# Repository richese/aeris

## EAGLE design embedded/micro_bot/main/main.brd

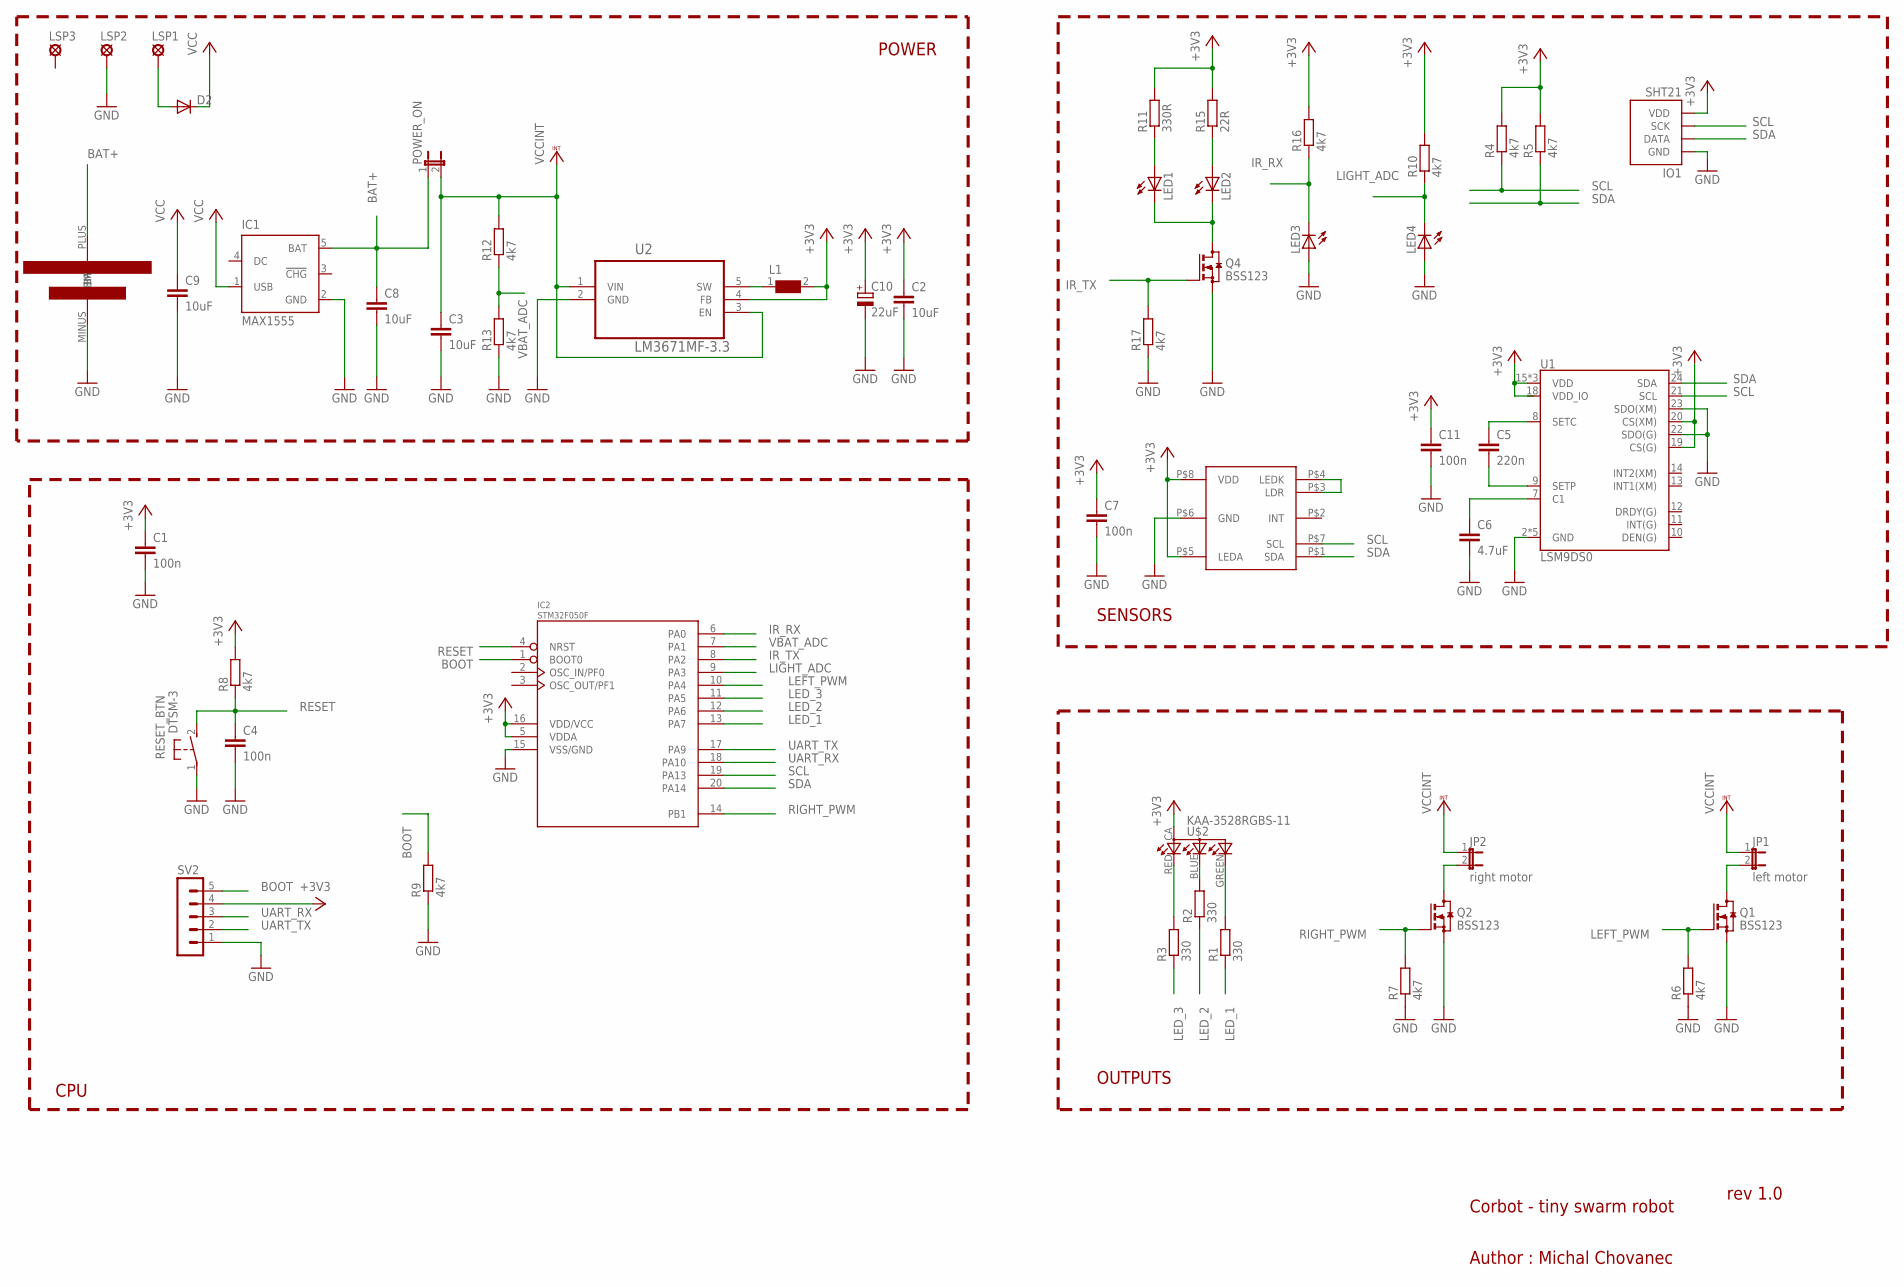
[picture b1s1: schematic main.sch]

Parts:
C1, C4, C7, C11: 100n; C0805
C2, C3, C8, C9: 10uF; C0805
C5: 220n; C0805
C6: 4.7uF; C0805
C10: 22uF; 153CLV-0505
D2: DIODE-DO-214AC; DO-214AC
IC1: MAX1555; SOT23-5L
IC2: STM32F050F; TSSOP20
IO1: SHT21; SHT2X
JP1: left motor; JP1
JP2: right motor; JP1
L1: WE-LQ-744032002_M; WE-LQ_M
LED1, LED2, LED3, LED4: LEDCHIPLED_1206; CHIPLED_1206
LSP1, LSP2, LSP3: LSP13
POWER_ON: JP1E; JP1
Q1, Q2, Q4: BSS123; SOT23
R1, R2, R3: 330; M0805
R4, R5, R6, R7, R8, R9, R10, R12, R13, R16, R17: 4k7; M0805
R11: 330R; M0805
R15: 22R; M0805
RESET_BTN: DTSM-3
SV2: MA05-1
U1: LSM9DS0; LGA-24
U2: LM3671MF-3.3; SOT95P284X122-5N
U$1: SMTU_2450N
U$2: KAA-3528RGBS-11; LED-RGB
U$3: APDS9950

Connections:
+3V3: C1.1, C2.1, C7.1, C10.+, C11.1, IC2.5 (VDDA), IC2.16 (VDD/VCC), IO1.5 (VDD), L1.2, R4.2, R5.2, R8.2, R10.2, R11.2, R15.2, R16.2, SV2.4, U1.15 (VDD), U1.16 (VDD), U1.17 (VDD), U1.19 (CS(G)), U1.20 (CS(XM)), U2.4 (FB), U$2.CA (A), U$3.P$5 (LEDA), U$3.P$8 (VDD)
BAT+: C8.1, IC1.5 (BAT), POWER_ON.1, U$1.PLUS (BP)
BOOT: IC2.1 (BOOT0), R9.2, SV2.5
GND: C1.2, C2.2, C3.2, C4.2, C6.2, C7.2, C8.2, C9.2, C10.-, C11.2, IC1.2 (GND), IC2.15 (VSS/GND), IO1.2 (GND), LED3.A, LED4.A, LSP2.MP, Q1.2 (S), Q2.2 (S), Q4.2 (S), R6.1, R7.1, R9.1, R13.1, R17.1, RESET_BTN.1, SV2.1, U1.2 (GND), U1.3 (GND), U1.4 (GND), U1.5 (GND), U1.6 (GND), U1.22 (SDO(G)), U1.23 (SDO(XM)), U2.2 (GND), U$1.MINUS (BM), U$3.P$6 (GND)
IR_RX: IC2.6 (PA0), LED3.C, R16.1
IR_TX: IC2.8 (PA2), Q4.1 (G), R17.2
LED_1: IC2.13 (PA7), R1.1
LED_2: IC2.12 (PA6), R2.1
LED_3: IC2.11 (PA5), R3.1
LEFT_PWM: IC2.10 (PA4), Q1.1 (G), R6.2
LIGHT_ADC: IC2.9 (PA3), LED4.C, R10.1
unnamed: R3.2, U$2.RED (CRED)
unnamed: R2.2, U$2.BLUE (CBLUE)
unnamed: R1.2, U$2.GREEN (CGREEN)
unnamed: U$3.P$3 (LDR), U$3.P$4 (LEDK)
unnamed: C6.1, U1.7 (C1)
unnamed: LED1.C, LED2.C, Q4.3 (D)
unnamed: L1.1, U2.5 (SW)
unnamed: C5.1, U1.8 (SETC)
unnamed: D2.A, LSP1.MP
unnamed: LED2.A, R15.1
unnamed: C5.2, U1.9 (SETP)
unnamed: JP1.2, Q1.3 (D)
unnamed: JP2.2, Q2.3 (D)
unnamed: LED1.A, R11.1
RESET: C4.1, IC2.4 (NRST), R8.1, RESET_BTN.2
RIGHT_PWM: IC2.14 (PB1), Q2.1 (G), R7.2
SCL: IC2.19 (PA13), IO1.4 (SCK), R4.1, U1.21 (SCL), U$3.P$7 (SCL)
SDA: IC2.20 (PA14), IO1.1 (DATA), R5.1, U1.24 (SDA), U$3.P$1 (SDA)
UART_RX: IC2.18 (PA10), SV2.3
UART_TX: IC2.17 (PA9), SV2.2
VBAT_ADC: IC2.7 (PA1), R12.1, R13.2
VCC: C9.1, D2.C, IC1.1 (USB)
VCCINT: C3.1, JP1.1, JP2.1, POWER_ON.2, R12.2, U2.1 (VIN), U2.3 (EN)

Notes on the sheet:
CPU
POWER
SENSORS
OUTPUTS
Corbot - tiny swarm robot
rev 1.0
Author : Michal Chovanec

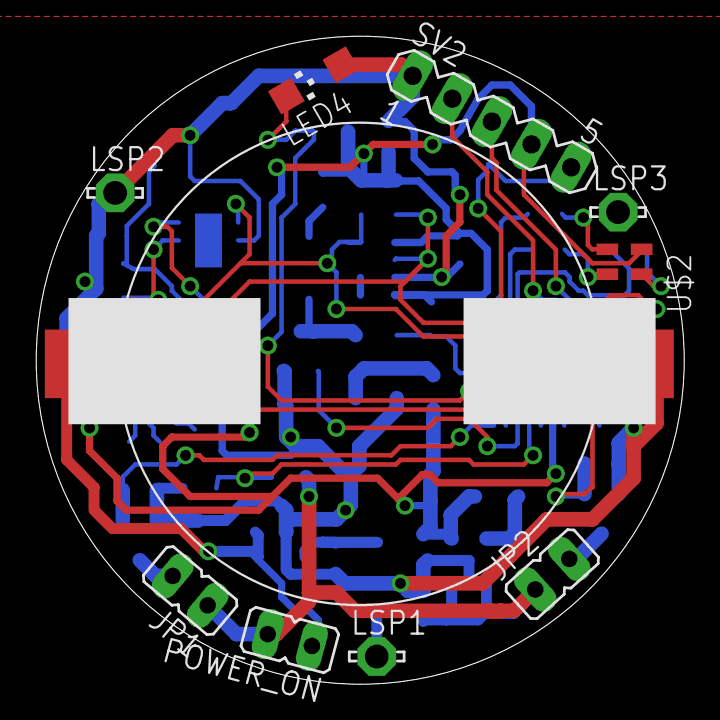
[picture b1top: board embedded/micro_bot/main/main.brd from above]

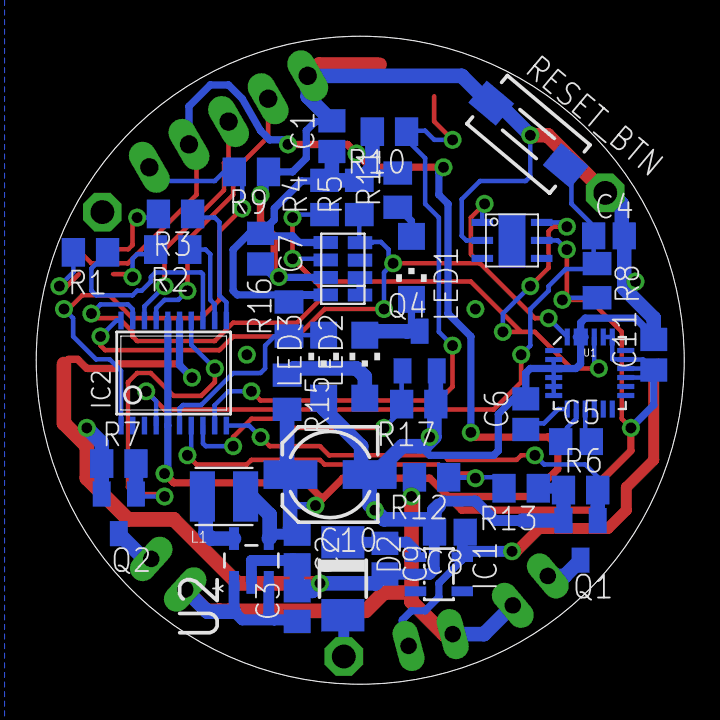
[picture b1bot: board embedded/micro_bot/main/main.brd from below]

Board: 2 copper layers, 36.0 x 36.0 mm, 52 parts (42 on the bottom side), 34 nets.

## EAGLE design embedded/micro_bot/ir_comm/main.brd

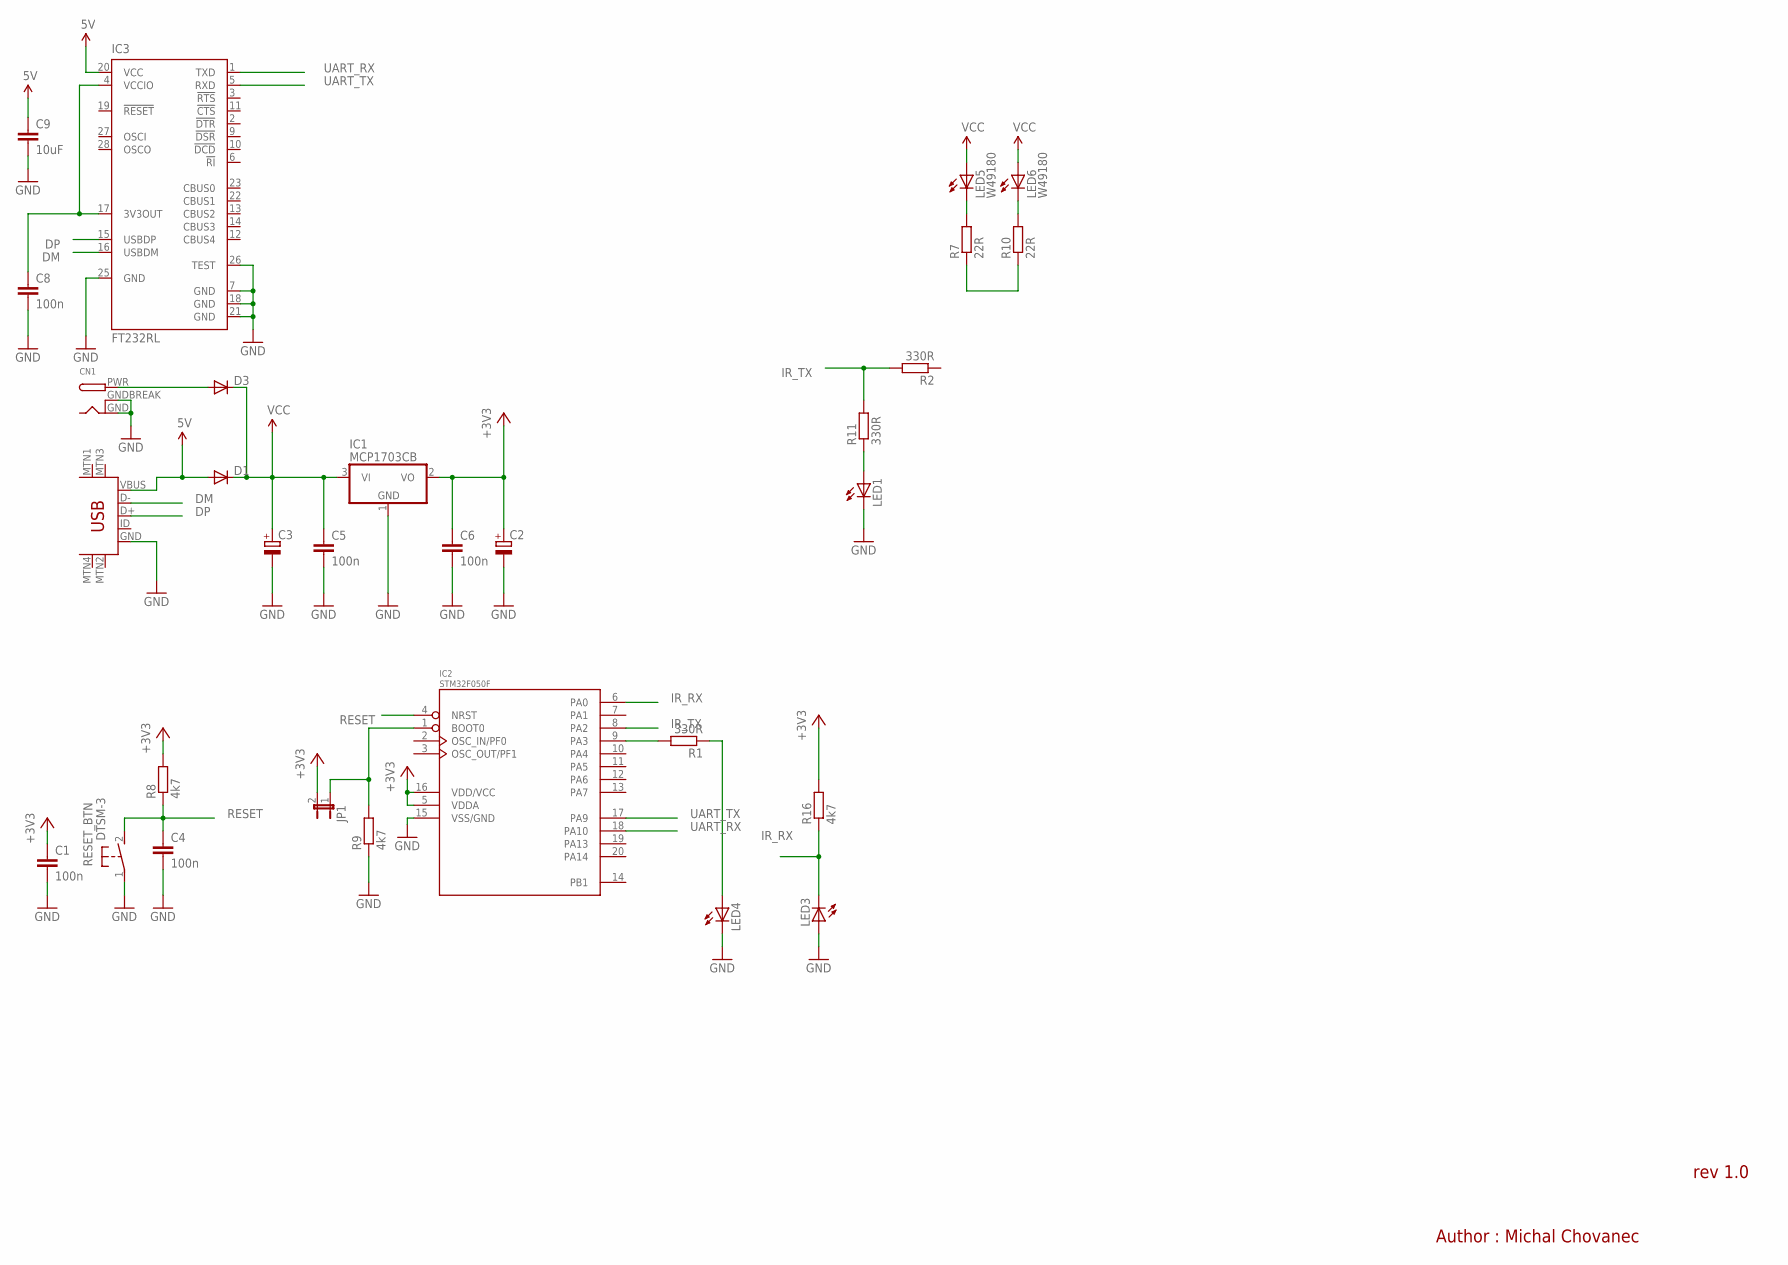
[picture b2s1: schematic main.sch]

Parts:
C1, C4, C5, C6, C8: 100n; C0805
C2: CPOL-EU153CLV-0405; 153CLV-0405
C3: CPOL-EU150CLZ-1010; 150CLZ-1010
C9: 10uF; C0805
CN1: DCBARRELPTH; DCJACK_2MM_PTH
D1, D3: DIODE-DO-214AC; DO-214AC
IC1: MCP1703CB; SOT23
IC2: STM32F050F; TSSOP20
IC3: FT232RL; SSOP28
JP1: JP1E; JP1
LED1, LED3, LED4: LEDCHIPLED_1206; CHIPLED_1206
LED5, LED6: W49180; Z-POWER-LED-DOME-TYPE
R1, R2, R11: 330R; M0805
R7, R10: 22R; M0805
R8, R9, R16: 4k7; M0805
RESET_BTN: DTSM-3
U$1: USB-MINIB-5PIN; USB-MINIB

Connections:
5V: C9.1, D1.A, IC3.20 (VCC), U$1.VBUS
+3V3: C1.1, C2.+, C6.1, IC1.2 (VO), IC2.5 (VDDA), IC2.16 (VDD/VCC), JP1.2, R8.2, R16.2
BOOT: IC2.1 (BOOT0), JP1.1, R9.2
DM: IC3.16 (USBDM), U$1.D-
DP: IC3.15 (USBDP), U$1.D+
GND: C1.2, C2.-, C3.-, C4.2, C5.2, C6.2, C8.2, C9.2, CN1.GND, CN1.GNDBREAK, IC1.1 (GND), IC2.15 (VSS/GND), IC3.7 (GND), IC3.18 (GND), IC3.21 (GND), IC3.25 (GND), IC3.26 (TEST), LED1.C, LED3.A, LED4.C, R9.1, RESET_BTN.1, U$1.GND
IR_RX: IC2.6 (PA0), LED3.C, R16.1
IR_TX: IC2.8 (PA2), R2.2, R11.2
unnamed: IC2.9 (PA3), R1.2
unnamed: C8.1, IC3.4 (VCCIO), IC3.17 (3V3OUT)
unnamed: LED1.A, R11.1
unnamed: CN1.PWR, D3.A
unnamed: LED4.A, R1.1
unnamed: LED5.C, R7.2
unnamed: LED6.C, R10.2
unnamed: R7.1, R10.1
RESET: C4.1, IC2.4 (NRST), R8.1, RESET_BTN.2
UART_RX: IC2.18 (PA10), IC3.1 (TXD)
UART_TX: IC2.17 (PA9), IC3.5 (RXD)
VCC: C3.+, C5.1, D1.C, D3.C, IC1.3 (VI), LED5.A, LED6.A

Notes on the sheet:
rev 1.0
Author : Michal Chovanec

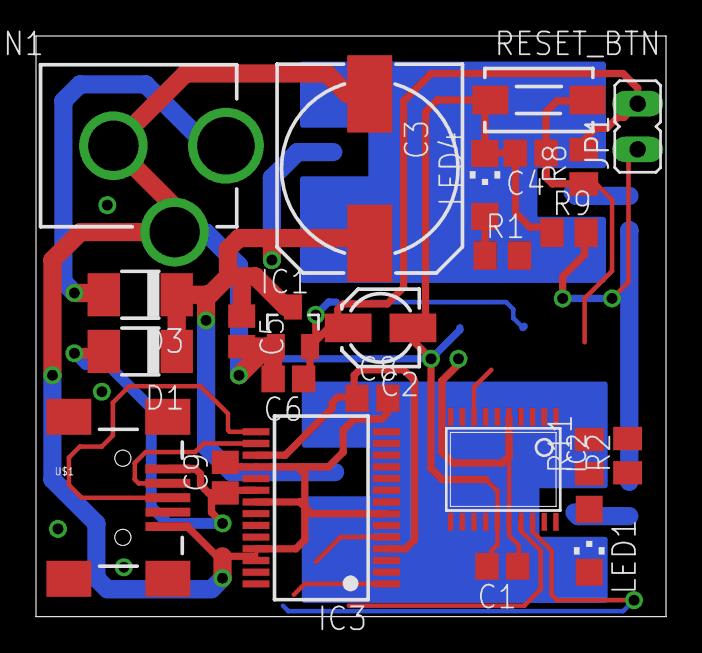
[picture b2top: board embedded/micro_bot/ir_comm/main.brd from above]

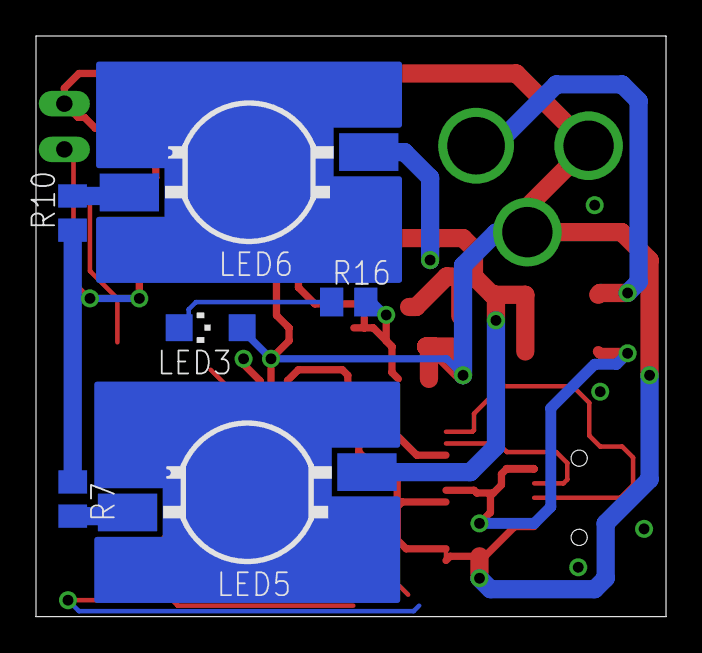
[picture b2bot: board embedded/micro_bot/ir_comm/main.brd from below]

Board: 2 copper layers, 35.0 x 32.3 mm, 30 parts (6 on the bottom side), 20 nets.

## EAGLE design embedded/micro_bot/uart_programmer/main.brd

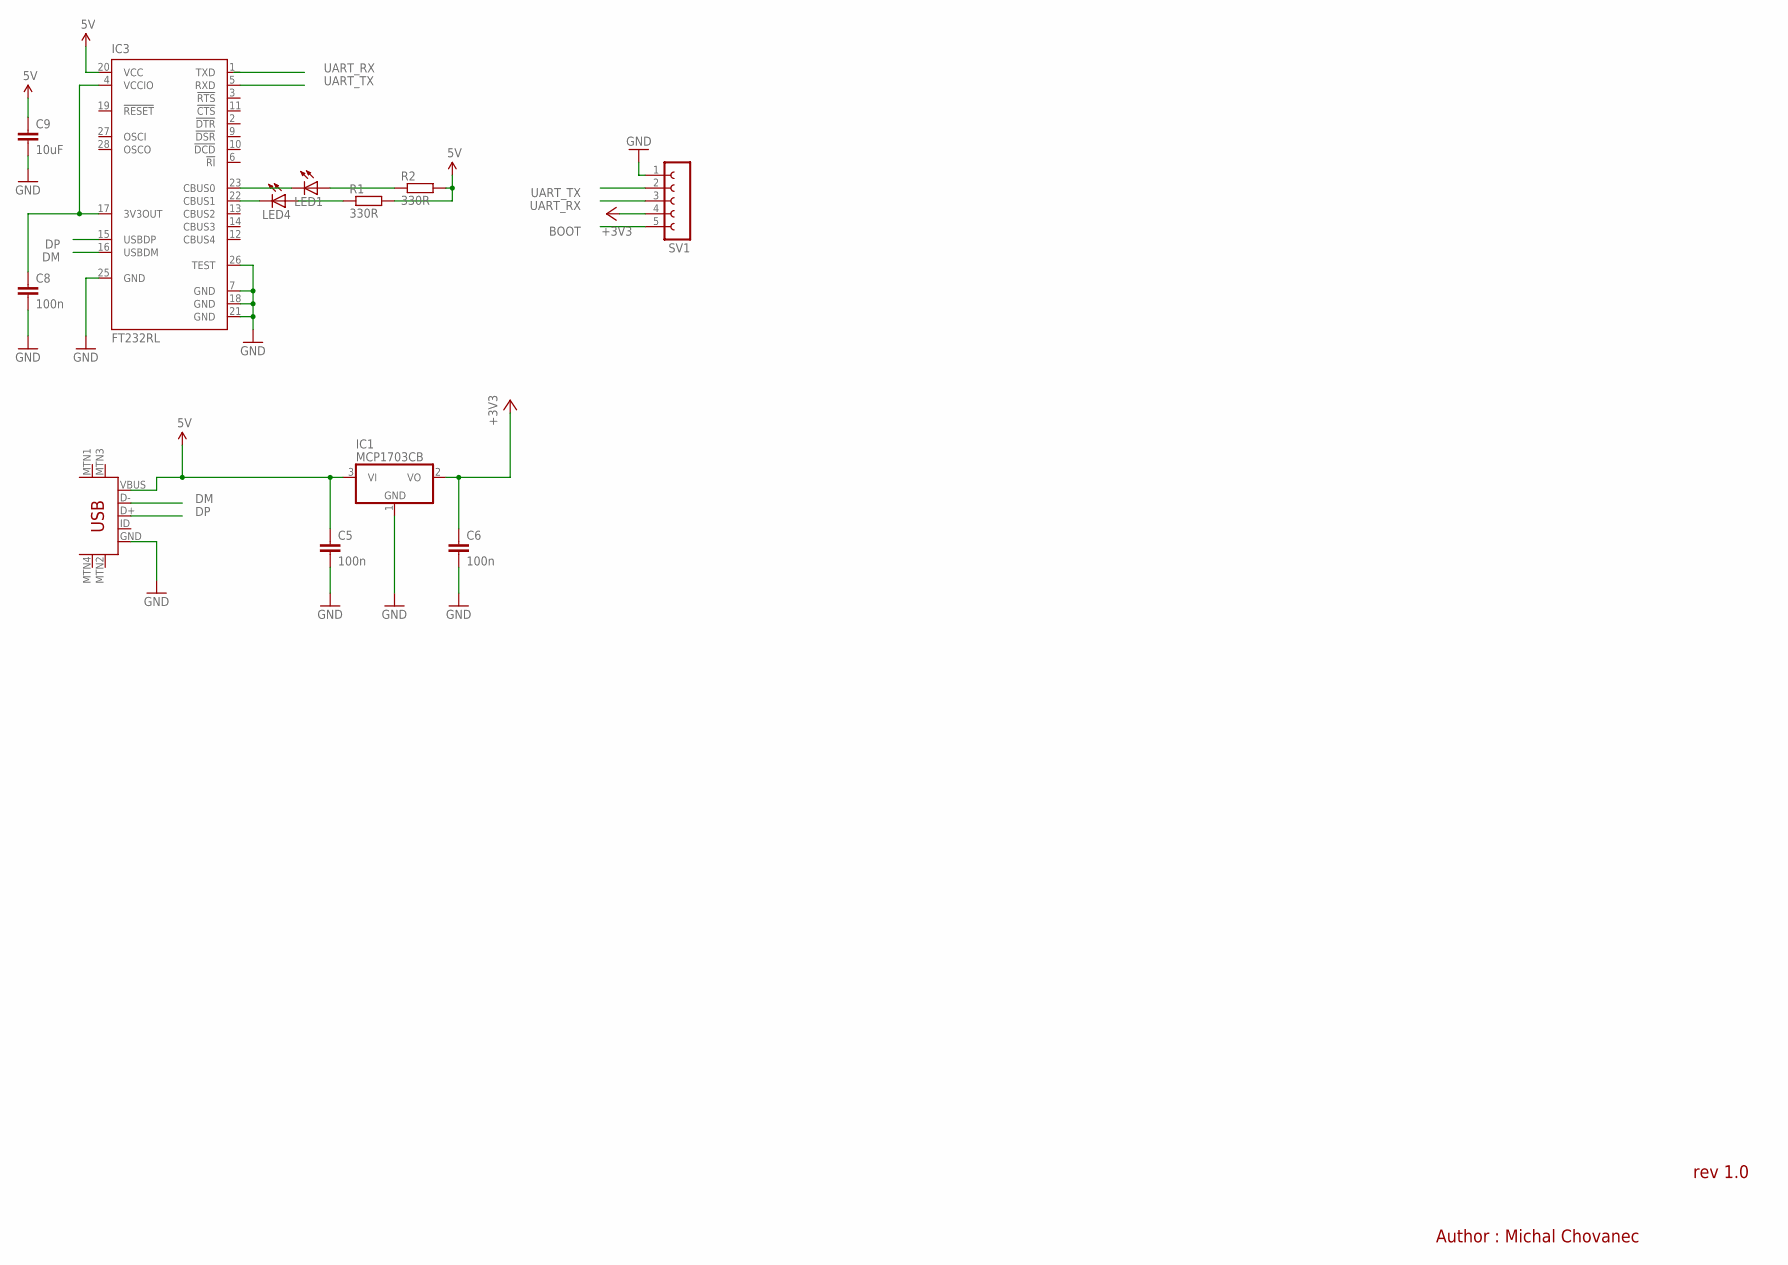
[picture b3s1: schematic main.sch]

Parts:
C5, C6, C8: 100n; C0805
C9: 10uF; C0805
IC1: MCP1703CB; SOT23
IC3: FT232RL; SSOP28
LED1, LED4: LEDCHIPLED_1206; CHIPLED_1206
R1, R2: 330R; M0805
SV1: FE05-1
U$1: USB-MINIB-5PIN; USB-MINIB

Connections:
5V: C5.1, C9.1, IC1.3 (VI), IC3.20 (VCC), R1.2, R2.2, U$1.VBUS
+3V3: C6.1, IC1.2 (VO), SV1.4
BOOT: SV1.5
DM: IC3.16 (USBDM), U$1.D-
DP: IC3.15 (USBDP), U$1.D+
GND: C5.2, C6.2, C8.2, C9.2, IC1.1 (GND), IC3.7 (GND), IC3.18 (GND), IC3.21 (GND), IC3.25 (GND), IC3.26 (TEST), SV1.1, U$1.GND
unnamed: IC3.23 (CBUS0), LED1.C
unnamed: C8.1, IC3.4 (VCCIO), IC3.17 (3V3OUT)
unnamed: IC3.22 (CBUS1), LED4.C
unnamed: LED4.A, R1.1
unnamed: LED1.A, R2.1
UART_RX: SV1.3
UART_TX: IC3.5 (RXD), SV1.2

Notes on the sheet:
rev 1.0
Author : Michal Chovanec

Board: 2 copper layers, 12 parts (0 on the bottom side), 11 nets, no tracks yet.

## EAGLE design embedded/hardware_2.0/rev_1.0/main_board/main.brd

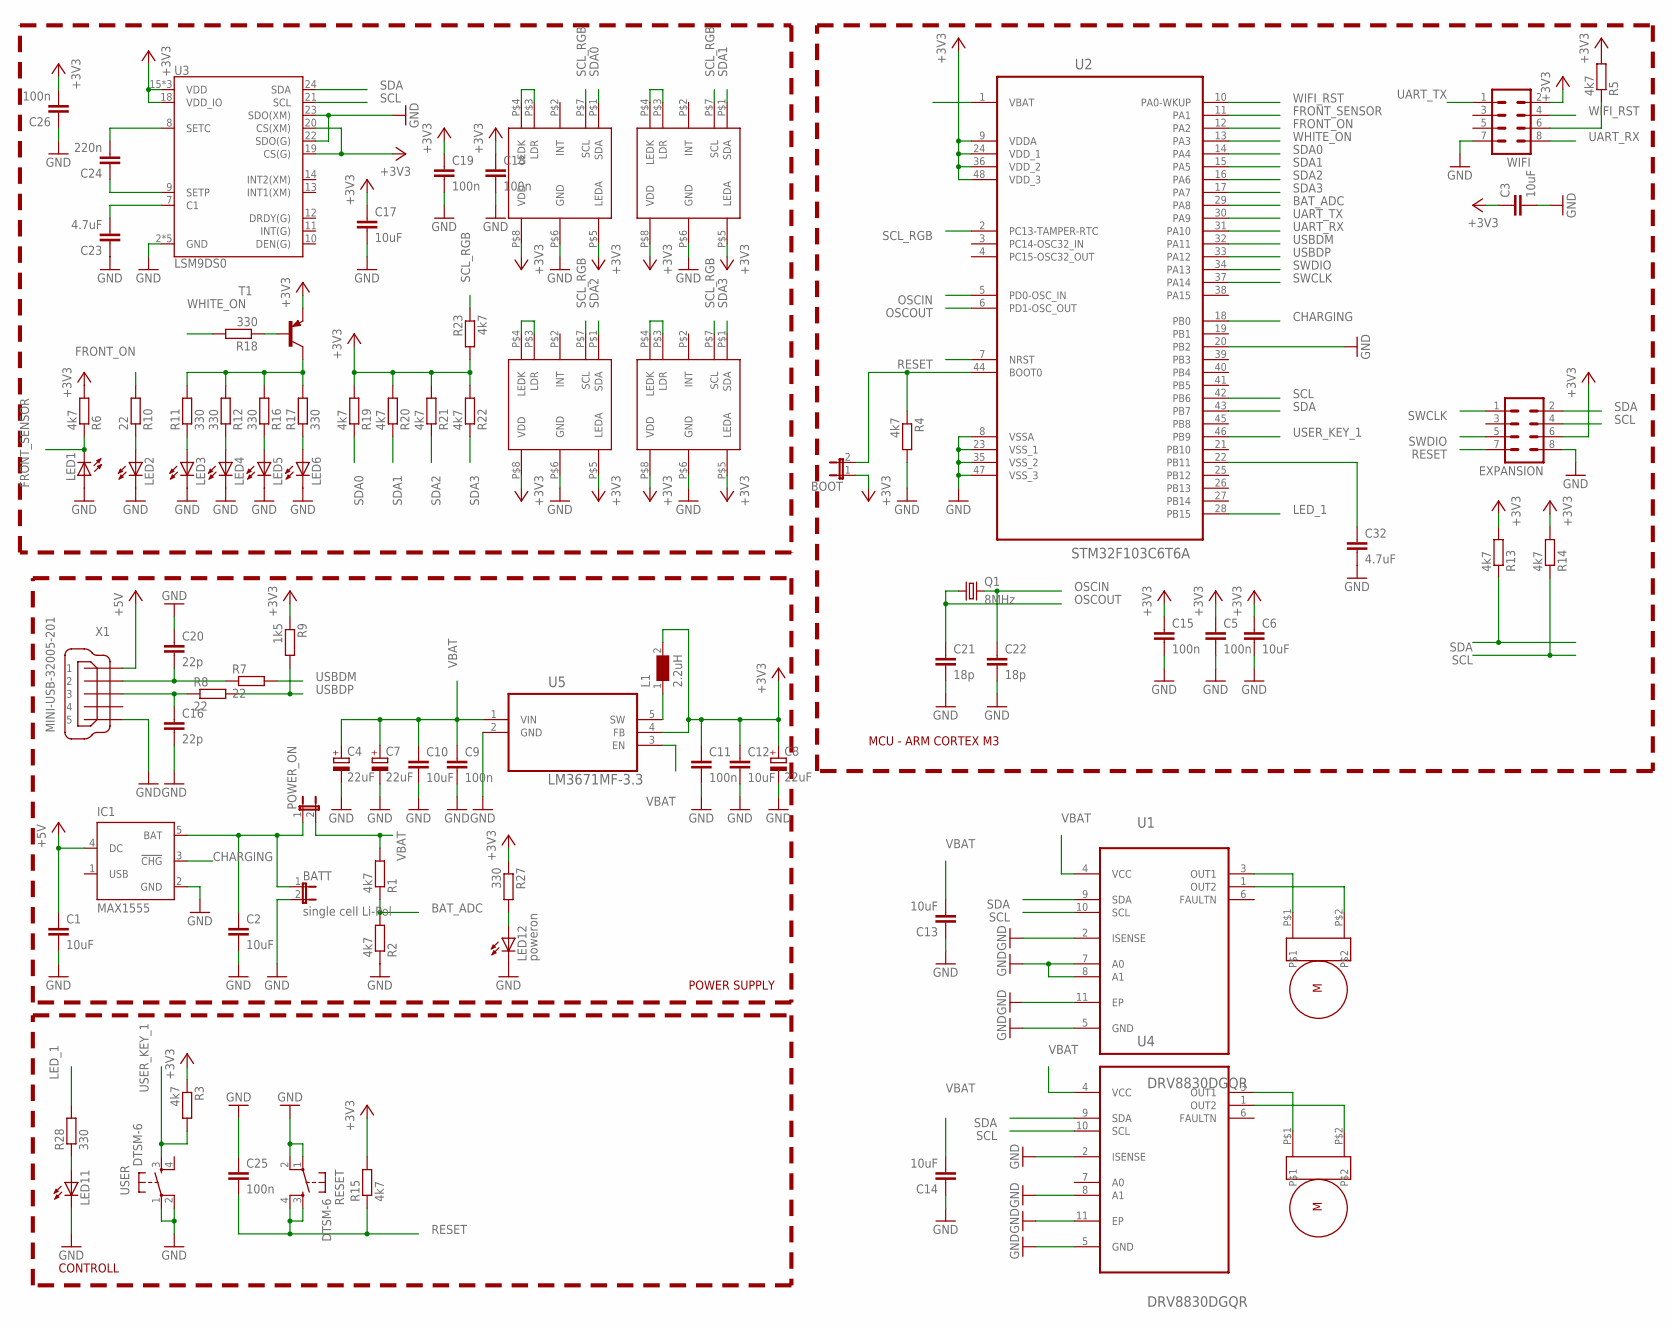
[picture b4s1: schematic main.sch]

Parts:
BATT: single cell Li-Pol; JP1
BOOT: JP1E; JP1
C1, C2, C3, C6, C10, C12, C13, C14, C17: 10uF; C0805
C4, C7, C8: 22uF; 153CLV-0505
C5, C9, C11, C15, C18, C19, C25, C26: 100n; C0805
C16, C20: 22p; C0805
C21, C22: 18p; C0805
C23, C32: 4.7uF; C0805
C24: 220n; C0805
EXPANSION: MA04-2
IC1: MAX1555; SOT23-5L
L1: 2.2uH; WE-LQ_M
LED1, LED2: LED5MM
LED3, LED4, LED5, LED6, LED11: LEDCHIPLED_1206; CHIPLED_1206
LED12: poweron; CHIPLED_1206
POWER_ON: JP1E; JP1
Q1: 8MHz; CTS406
R1, R2, R3, R4, R5, R6, R13, R14, R15, R19, R20, R21, R22, R23: 4k7; M0805
R7, R8, R10: 22; M0805
R9: 1k5; M0805
R11, R12, R16, R17, R18, R27, R28: 330; M0805
RESET: DTSM-6
T1: BC857A-PNP-SOT23-BEC; SOT23-BEC
U1, U4: DRV8830DGQR; SOP65P640X110-15N
U2: STM32F103C6T6A; QFP50P900X900X160-48N
U3: LSM9DS0; LGA-24
U5: LM3671MF-3.3; SOT95P284X122-5N
U$1, U$2, U$3, U$4: APDS9950
U$5, U$6: MICRO_METAL_GEAR_MOTOR
USER: DTSM-6
WIFI: MA04-2
X1: MINI-USB-32005-201; 32005-201

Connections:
+3V3: BOOT.1, C3.1, C5.1, C6.1, C8.+, C11.1, C12.1, C15.1, C17.1, C18.1, C19.1, C26.2, EXPANSION.6, L1.2, R3.1, R5.2, R6.2, R9.1, R13.2, R14.2, R15.2, R19.2, R20.2, R21.2, R22.2, R23.2, R27.1, T1.E, U2.9 (VDDA), U2.24 (VDD_1), U2.36 (VDD_2), U2.48 (VDD_3), U3.15 (VDD), U3.16 (VDD), U3.17 (VDD), U3.18 (VDD_IO), U3.19 (CS(G)), U3.20 (CS(XM)), U5.4 (FB), U$1.P$5 (LEDA), U$1.P$8 (VDD), U$2.P$5 (LEDA), U$2.P$8 (VDD), U$3.P$5 (LEDA), U$3.P$8 (VDD), U$4.P$5 (LEDA), U$4.P$8 (VDD), WIFI.2
+5V: C1.1, IC1.4 (DC), X1.1
BAT_ADC: R1.1, R2.2, U2.29 (PA8)
CHARGING: IC1.3 (!CHG), U2.18 (PB0)
FRONT_ON: R10.2, U2.12 (PA2)
FRONT_SENSOR: LED1.K (C), R6.1, U2.11 (PA1)
GND: BATT.2, C1.2, C2.2, C3.2, C4.-, C5.2, C6.2, C7.-, C8.-, C9.2, C10.2, C11.2, C12.2, C13.1, C14.1, C15.2, C16.2, C17.2, C18.2, C19.2, C20.1, C21.2, C22.2, C23.1, C25.1, C26.1, C32.2, EXPANSION.8, IC1.2 (GND), LED1.A, LED2.K (C), LED3.C, LED4.C, LED5.C, LED6.C, LED11.C, LED12.C, R2.1, R4.2, RESET.1, RESET.2, U1.2 (ISENSE), U1.5 (GND), U1.7 (A0), U1.8 (A1), U1.11 (EP), U2.8 (VSSA), U2.20 (PB2), U2.23 (VSS_1), U2.35 (VSS_2), U2.47 (VSS_3), U3.2 (GND), U3.3 (GND), U3.4 (GND), U3.5 (GND), U3.6 (GND), U3.22 (SDO(G)), U3.23 (SDO(XM)), U4.2 (ISENSE), U4.5 (GND), U4.8 (A1), U4.11 (EP), U5.2 (GND), U$1.P$6 (GND), U$2.P$6 (GND), U$3.P$6 (GND), U$4.P$6 (GND), USER.1, USER.2, WIFI.7, X1.5
LED_1: R28.2, U2.28 (PB15)
unnamed: R5.1, WIFI.6
unnamed: BATT.1, C2.1, IC1.5 (BAT), POWER_ON.1
unnamed: U1.1 (OUT2), U$5.P$2
unnamed: U1.3 (OUT1), U$5.P$1
unnamed: U4.1 (OUT2), U$6.P$2
unnamed: C23.2, U3.7 (C1)
unnamed: C24.2, U3.8 (SETC)
unnamed: U4.3 (OUT1), U$6.P$1
unnamed: L1.1, U5.5 (SW)
unnamed: C24.1, U3.9 (SETP)
unnamed: C32.1, U2.22 (PB11)
unnamed: LED3.A, R11.1
unnamed: BOOT.2, R4.1, U2.44 (BOOT0)
unnamed: U$1.P$3 (LDR), U$1.P$4 (LEDK)
unnamed: U$2.P$3 (LDR), U$2.P$4 (LEDK)
unnamed: U$3.P$3 (LDR), U$3.P$4 (LEDK)
unnamed: U$4.P$3 (LDR), U$4.P$4 (LEDK)
unnamed: LED2.A, R10.1
unnamed: LED4.A, R12.1
unnamed: LED12.A, R27.2
unnamed: LED5.A, R16.1
unnamed: LED6.A, R17.1
unnamed: R11.2, R12.2, R16.2, R17.2, T1.C
unnamed: R18.1, T1.B
unnamed: LED11.A, R28.1
unnamed: C20.2, R7.1, X1.2
unnamed: C16.1, R8.1, X1.3
NC: U2.1 (VBAT)
OSCIN: C22.1, Q1.3 (2), U2.5 (PD0-OSC_IN)
OSCOUT: C21.1, Q1.1, U2.6 (PD1-OSC_OUT)
RESET: C25.2, EXPANSION.7, R15.1, RESET.3, RESET.4, U2.7 (NRST)
SCL: EXPANSION.4, R14.1, U1.10 (SCL), U2.42 (PB6), U3.21 (SCL), U4.10 (SCL)
SCL_RGB: R23.1, U2.2 (PC13-TAMPER-RTC), U$1.P$7 (SCL), U$2.P$7 (SCL), U$3.P$7 (SCL), U$4.P$7 (SCL)
SDA: EXPANSION.2, R13.1, U1.9 (SDA), U2.43 (PB7), U3.24 (SDA), U4.9 (SDA)
SDA0: R19.1, U2.14 (PA4), U$1.P$1 (SDA)
SDA1: R20.1, U2.15 (PA5), U$2.P$1 (SDA)
SDA2: R21.1, U2.16 (PA6), U$3.P$1 (SDA)
SDA3: R22.1, U2.17 (PA7), U$4.P$1 (SDA)
SWCLK: EXPANSION.1, U2.37 (PA14)
SWDIO: EXPANSION.5, U2.34 (PA13)
UART_RX: U2.31 (PA10), WIFI.8
UART_TX: U2.30 (PA9), WIFI.1
USBDM: R7.2, U2.32 (PA11)
USBDP: R8.2, R9.2, U2.33 (PA12)
USER_KEY_1: R3.2, U2.46 (PB9), USER.3
VBAT: C4.+, C7.+, C9.1, C10.1, C13.2, C14.2, POWER_ON.2, R1.2, U1.4 (VCC), U4.4 (VCC), U5.1 (VIN), U5.3 (EN)
WHITE_ON: R18.2, U2.13 (PA3)
WIFI_RST: U2.10 (PA0-WKUP), WIFI.4

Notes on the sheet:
POWER SUPPLY
CONTROLL
MCU - ARM CORTEX M3

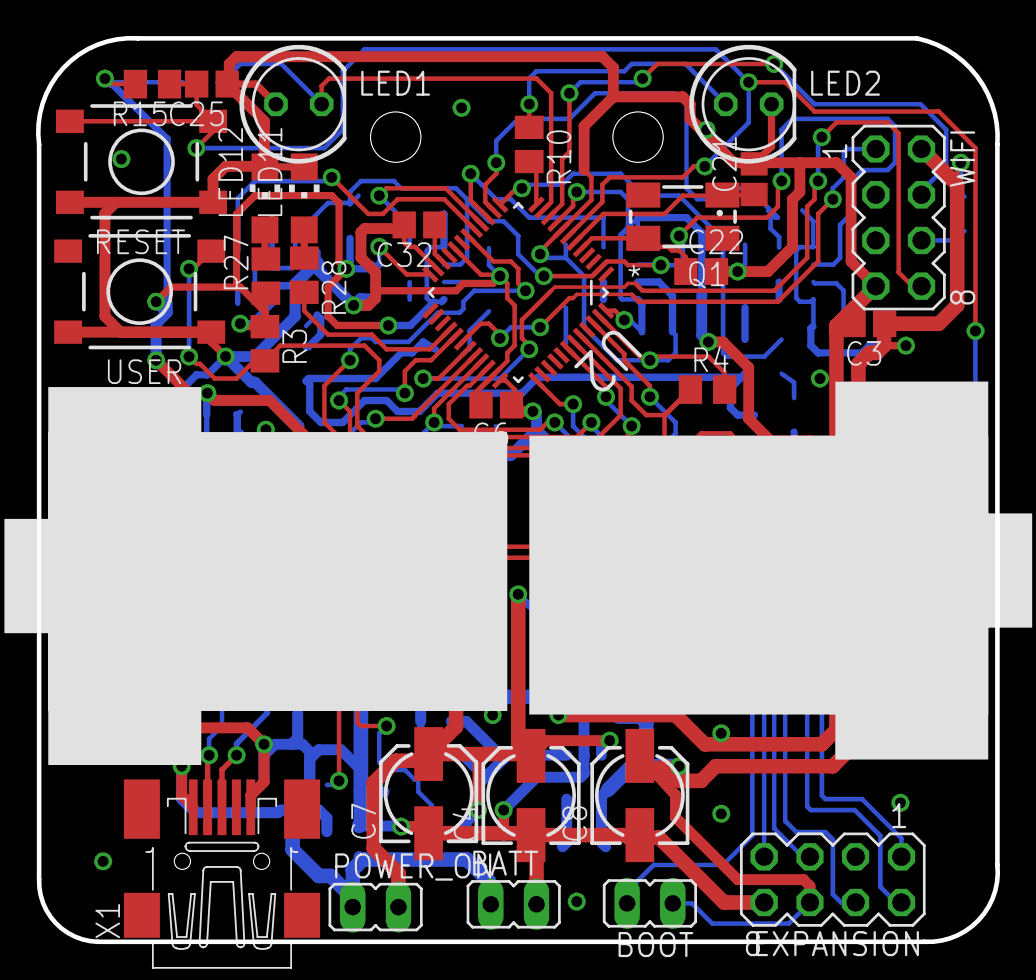
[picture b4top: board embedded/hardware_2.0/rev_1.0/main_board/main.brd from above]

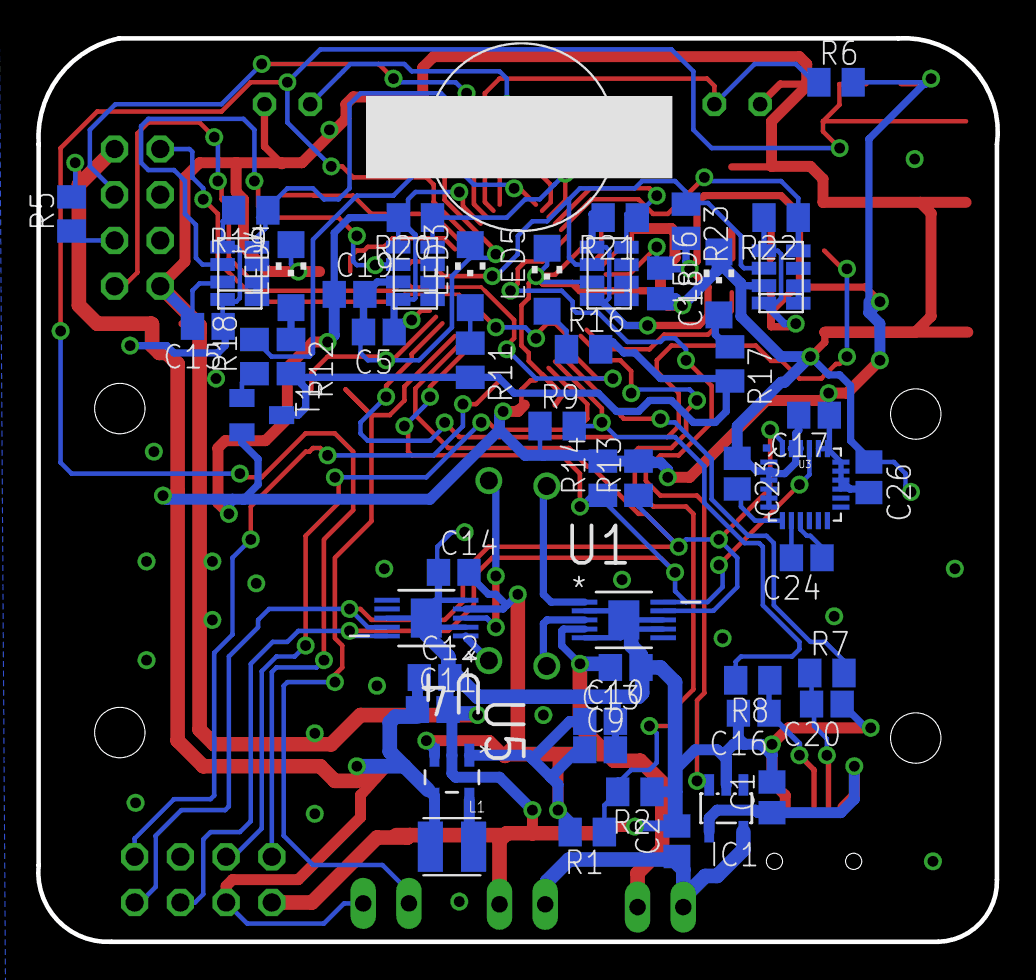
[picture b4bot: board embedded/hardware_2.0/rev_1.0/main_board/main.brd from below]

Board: 2 copper layers, 53.3 x 50.2 mm, 84 parts (53 on the bottom side), 55 nets.

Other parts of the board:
U$7: BALL_3/8

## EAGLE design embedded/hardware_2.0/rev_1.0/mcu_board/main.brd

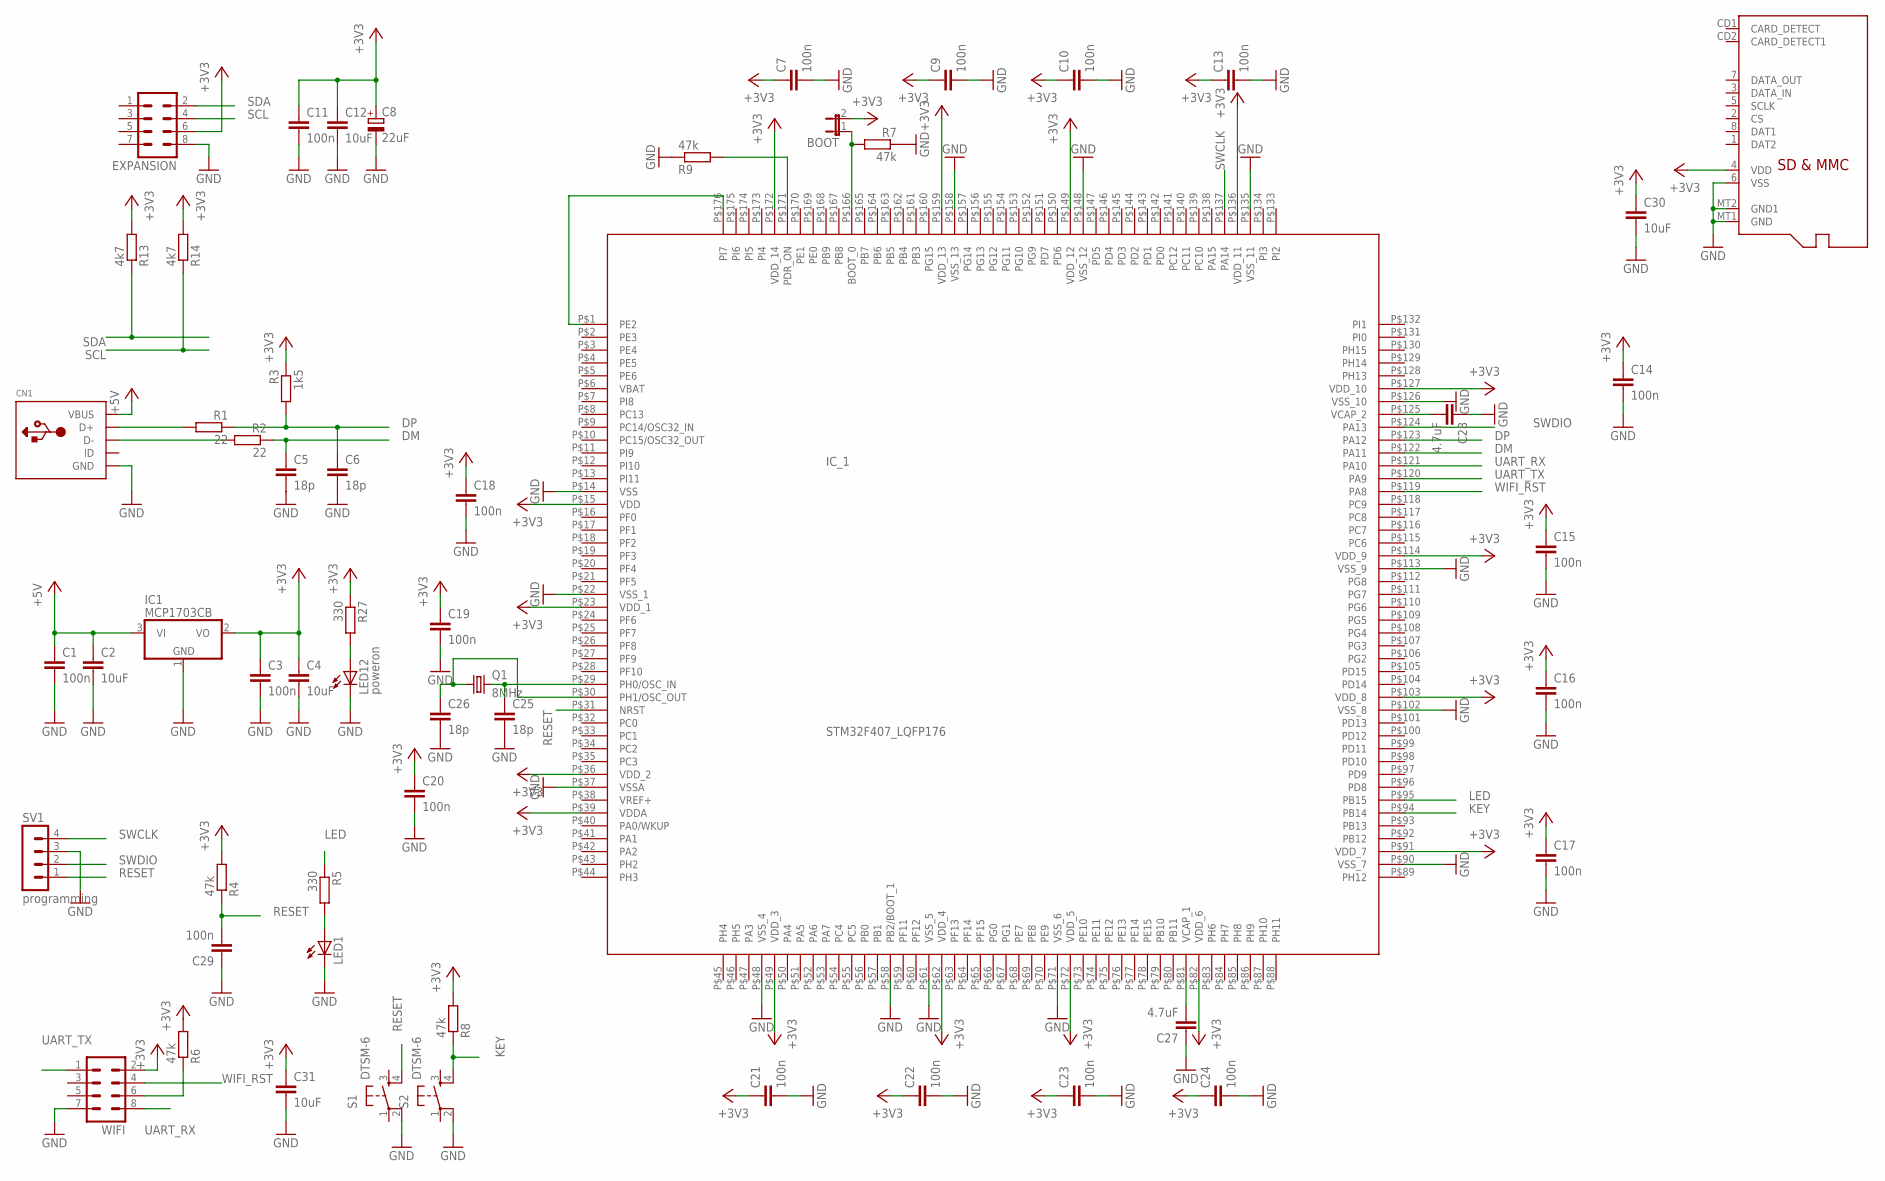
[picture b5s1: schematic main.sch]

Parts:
BOOT: JP1E; JP1
C1, C3, C7, C9, C10, C11, C13, C14, C15, C16, C17, C18, C19, C20, C21, C22, C23, C24, C29: 100n; C0805
C2, C4, C12, C30, C31: 10uF; C0805
C5, C6, C25, C26: 18p; C0805
C8: 22uF; 153CLV-0505
C27, C28: 4.7uF; C0805
CN1: USBMINIB; USB-MINIB
EXPANSION: MA04-2
IC1: MCP1703CB; SOT23
IC_1: STM32F407_LQFP176
LED1: LEDCHIPLED_1206; CHIPLED_1206
LED12: poweron; CHIPLED_1206
Q1: 8MHz; CTS406
R1, R2: 22; M0805
R3: 1k5; M0805
R4, R6, R7, R8, R9: 47k; M0805
R5, R27: 330; M0805
R13, R14: 4k7; M0805
S1, S2: DTSM-6
SV1: programming; MA04-1
U$1: MICROSD
WIFI: MA04-2

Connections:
+3V3: BOOT.2, C3.1, C4.1, C7.1, C8.+, C9.1, C10.1, C11.1, C12.1, C13.1, C14.1, C15.1, C16.1, C17.1, C18.1, C19.1, C20.1, C21.1, C22.1, C23.1, C24.1, C30.1, C31.1, EXPANSION.6, IC1.2 (VO), IC_1.P$15 (VDD), IC_1.P$23 (VDD_1), IC_1.P$36 (VDD_2), IC_1.P$39 (VDDA), IC_1.P$49 (VDD_3), IC_1.P$62 (VDD_4), IC_1.P$72 (VDD_5), IC_1.P$82 (VDD_6), IC_1.P$91 (VDD_7), IC_1.P$103 (VDD_8), IC_1.P$114 (VDD_9), IC_1.P$127 (VDD_10), IC_1.P$136 (VDD_11), IC_1.P$149 (VDD_12), IC_1.P$159 (VDD_13), IC_1.P$172 (VDD_14), R3.1, R4.2, R6.2, R8.2, R13.2, R14.2, R27.1, U$1.4 (VDD), WIFI.2
+5V: C1.1, C2.1, CN1.VBUS, IC1.3 (VI)
DM: C5.1, IC_1.P$122 (PA11), R2.1
DP: C6.1, IC_1.P$123 (PA12), R1.1, R3.2
GND: C1.2, C2.2, C3.2, C4.2, C5.2, C6.2, C7.2, C8.-, C9.2, C10.2, C11.2, C12.2, C13.2, C14.2, C15.2, C16.2, C17.2, C18.2, C19.2, C20.2, C21.2, C22.2, C23.2, C24.2, C25.2, C26.2, C27.1, C28.1, C29.1, C30.2, C31.2, CN1.GND, EXPANSION.8, IC1.1 (GND), IC_1.P$14 (VSS), IC_1.P$22 (VSS_1), IC_1.P$37 (VSSA), IC_1.P$48 (VSS_4), IC_1.P$58 (PB2/BOOT_1), IC_1.P$61 (VSS_5), IC_1.P$71 (VSS_6), IC_1.P$90 (VSS_7), IC_1.P$102 (VSS_8), IC_1.P$113 (VSS_9), IC_1.P$126 (VSS_10), IC_1.P$135 (VSS_11), IC_1.P$148 (VSS_12), IC_1.P$158 (VSS_13), LED1.C, LED12.C, R7.1, R9.1, S1.2, S2.2, SV1.3, U$1.6 (VSS), U$1.MT1 (GND), U$1.MT2 (GND1), WIFI.7
KEY: IC_1.P$94 (PB14), R8.1, S2.4
LED: IC_1.P$95 (PB15), R5.1
unnamed: CN1.D+, R1.2
unnamed: CN1.D-, R2.2
unnamed: C25.1, IC_1.P$29 (PH0/OSC_IN), Q1.3 (2)
unnamed: C26.1, IC_1.P$30 (PH1/OSC_OUT), Q1.1
unnamed: C27.2, IC_1.P$81 (VCAP_1)
unnamed: C28.2, IC_1.P$125 (VCAP_2)
unnamed: LED1.A, R5.2
unnamed: R6.1, WIFI.6
unnamed: BOOT.1, IC_1.P$166 (BOOT_0), R7.2
unnamed: IC_1.P$171 (PDR_ON), R9.2
unnamed: IC_1.P$1 (PE2), IC_1.P$176 (PI7)
unnamed: LED12.A, R27.2
RESET: C29.2, IC_1.P$31 (NRST), R4.1, S1.4, SV1.1
SCL: EXPANSION.4, R14.1
SDA: EXPANSION.2, R13.1
SWCLK: IC_1.P$137 (PA14), SV1.4
SWDIO: IC_1.P$124 (PA13), SV1.2
UART_RX: IC_1.P$121 (PA10), WIFI.8
UART_TX: IC_1.P$120 (PA9), WIFI.1
VBAT: IC_1.P$6 (VBAT)
VREF+: IC_1.P$38 (VREF+)
WIFI_RST: IC_1.P$119 (PA8), WIFI.4

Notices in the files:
parts and their libraries:
SparkFun-Sensors_03: Licensing: Creative Commons ShareAlike 4.0 International - https://creativecommons.org/licenses/by-sa/4.0
SparkFun: Licensing: CC v3.0 Share-Alike You are welcome to use this library for commercial purposes.
